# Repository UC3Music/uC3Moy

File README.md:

uC3Moy
======

UC3Music-e version of the CMoy pocket headphone amplifier (originally designed by Chu Moy )

Designed to fit in to a Smint* can.
Smint sweets can inner dimensions: 69mm x 36mm x 17mm. Outer dimensions: 77mm x 40mm x 21mm.

Designed to work on a single 6LR61 9V battery (alcaline or rechargeable). Draws about 8mA of current at regular listening levels (13mA at full output). Lithium technology coming soon.

It might get loud, use responsibly.

>*Smint is a mint sweet similar to Wrigley's Eclipse

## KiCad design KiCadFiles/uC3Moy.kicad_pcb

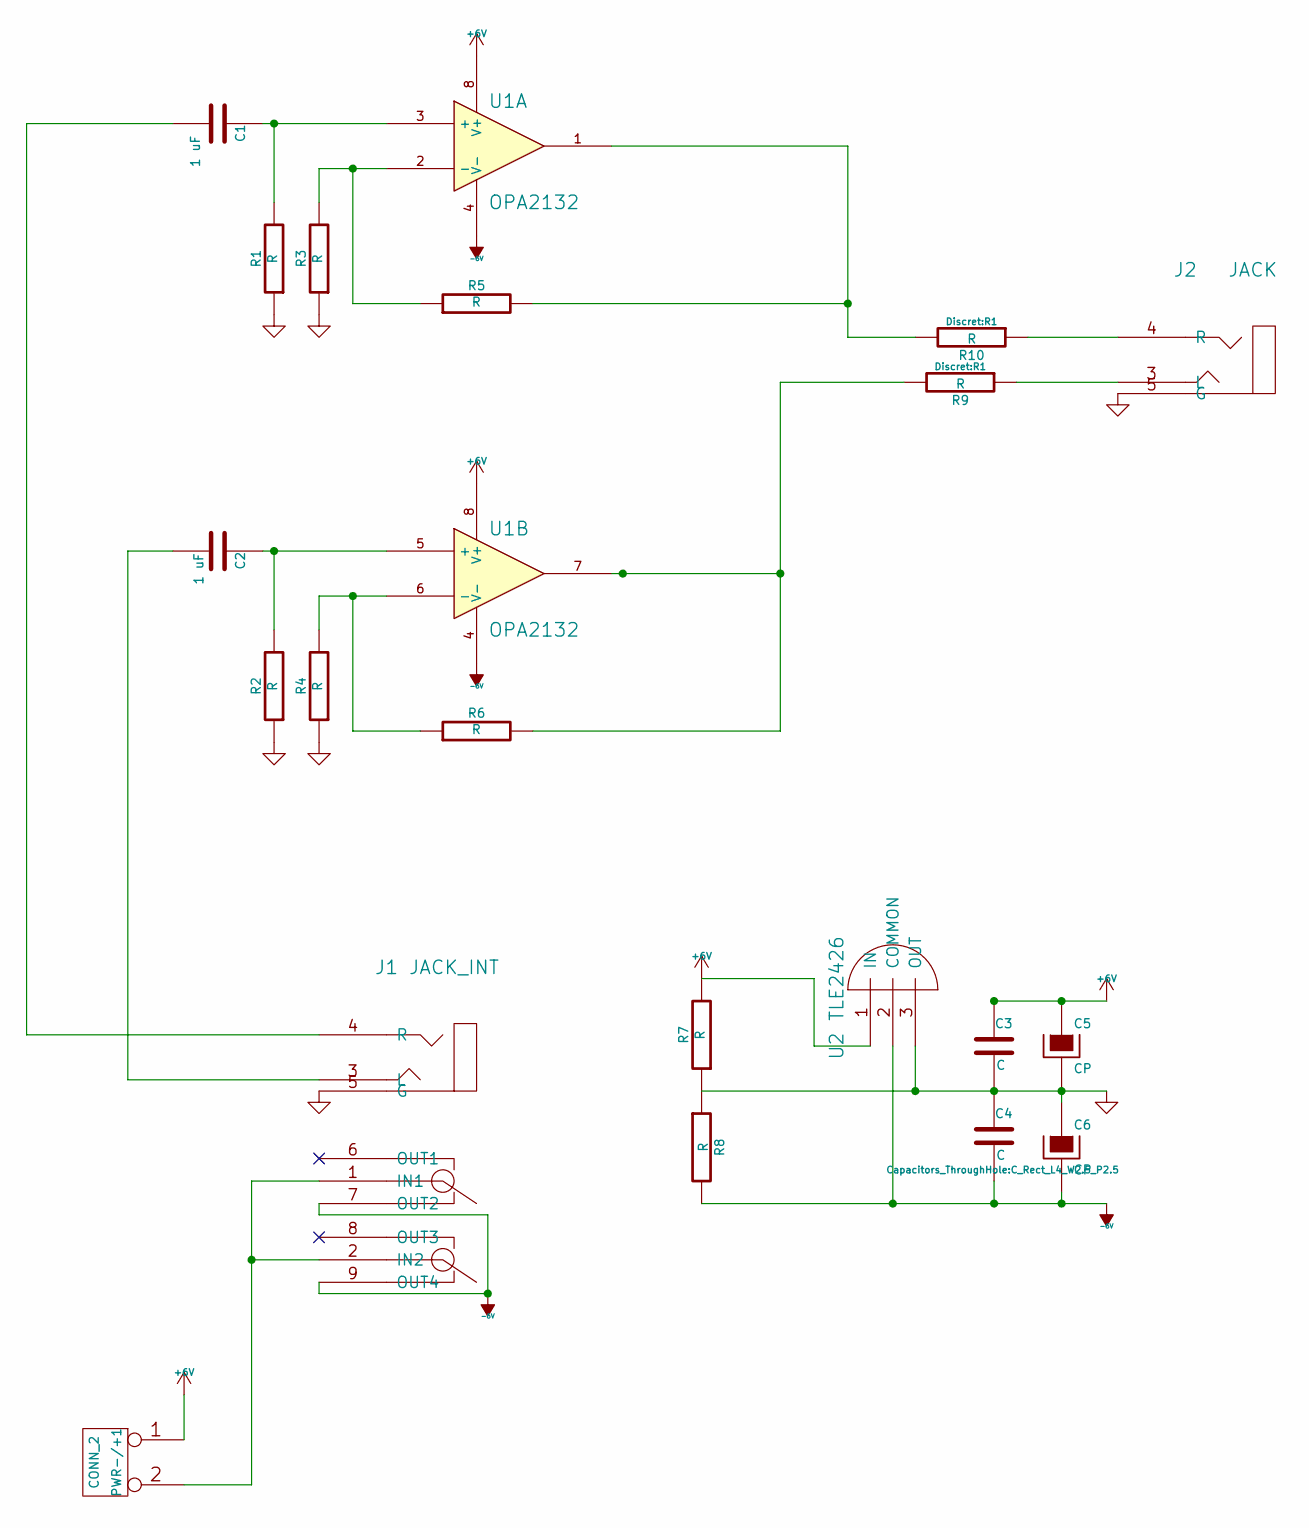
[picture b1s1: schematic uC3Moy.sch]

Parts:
C1, C2: 1 uF; C_Rect_L7_W2.5_P5
C3, C4: C; C_Rect_L4_W2.5_P2.5
C5, C6: CP; C_Radial_D5_L6_P2.5
J1: JACK_INT; jackint
J2: JACK; jack
PWR-/+1: CONN_2; Pin_Header_Straight_1x02
R1, R2, R3, R4, R5, R6, R7, R8, R9, R10: R; R1
U1: OPA2132; DIP-8_W7.62mm_jorfru
U2: TLE2426; TO-92_Inline_Wide

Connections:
+6V: C3.1, C5.1, PWR-/+1.1, R7.2, U1.8 (V+), U2.1 (IN)
-6V: C4.2, C6.2, J1.7 (OUT2), J1.9 (OUT4), R8.2, U1.4 (V-), U2.2 (COMMON)
GND: C3.2, C4.1, C5.2, C6.1, J1.5 (G), J2.5 (G), R1.1, R2.1, R3.1, R4.1, R7.1, R8.1, U2.3 (OUT)
unnamed: C1.1, R1.2, U1.3 (+)
unnamed: C1.2, J1.4 (R)
unnamed: C2.1, R2.2, U1.5 (+)
unnamed: C2.2, J1.3 (L)
unnamed: J1.1 (IN1), J1.2 (IN2), PWR-/+1.2 (PM)
unnamed: J2.3 (L), R9.1
unnamed: J2.4 (R), R10.1
unnamed: R3.2, R5.1, U1.2 (-)
unnamed: R4.2, R6.1, U1.6 (-)
unnamed: R6.2, R9.2, U1.7
unnamed: R5.2, R10.2, U1.1

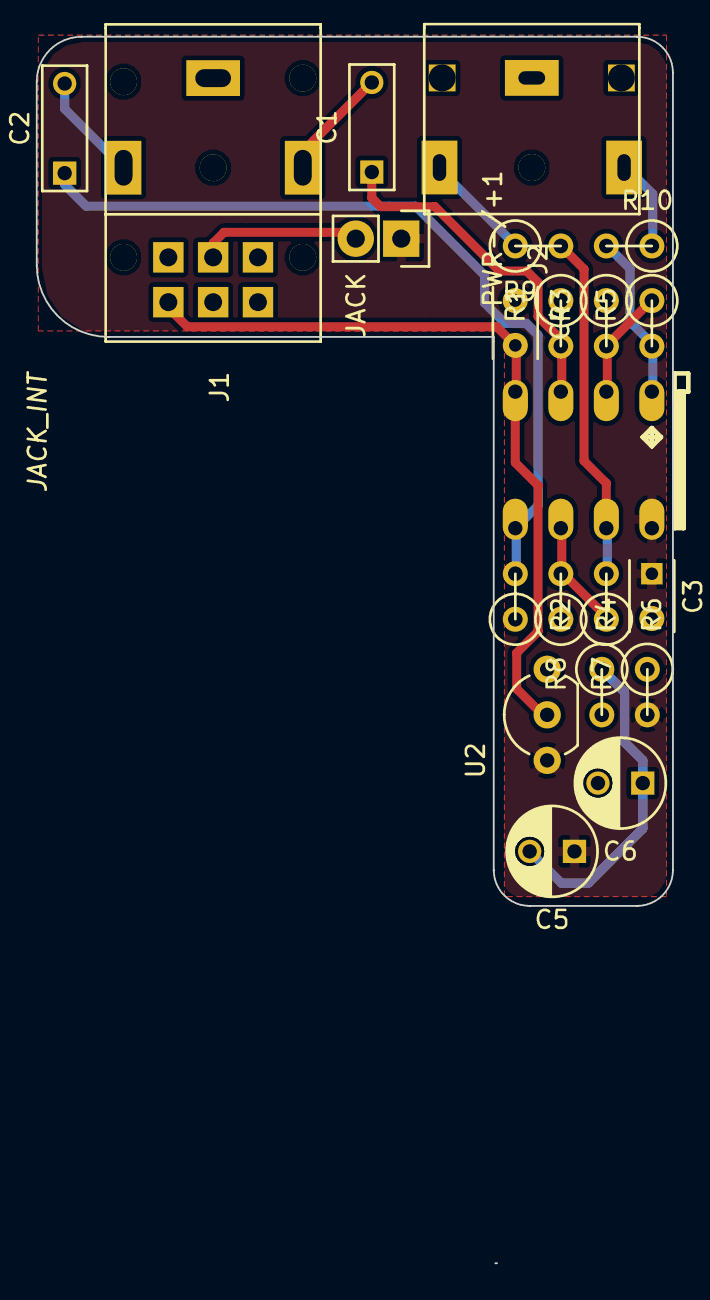
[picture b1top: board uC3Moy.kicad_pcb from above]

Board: 2 copper layers, 35.5 x 68.4 mm, 21 parts (0 on the bottom side), 14 nets.

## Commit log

2014-11-22 Added schematic (without connectors).
2014-11-22 Added gitignore for *.bak files
2015-03-02 Commit subiendo el diseño principal
2015-03-02 General UPLOAD
    PCB folder created.
    >Media folder containing .jpg images of PCB created.
    >KiCadFiles folder containing KiCad files of PCB created.
    >gerber folder containing gerber files of PCB created.
    A .pdf file containing a drawing of the schematic added.
2015-03-06 README revision
2015-03-06 Schematic on .pdf added to Media folder
2015-03-14 Modified lenght to fit under 50x50mm boards
2015-03-15 redo gerbers
2015-03-15 Silkscreen upgrades
2015-03-16 guitar logo added to back silkscreen
2015-03-17 Updates in bottom silkescreen
2015-03-17 updated gerbers
2015-03-17 With logo
2015-03-19 substracted soldermask from silkscreen
2015-03-19 v0.1 gerber files sended to SeeedStudio
2015-07-11 Added photos and media
2015-11-04 savepoint
2015-11-05 Ready to rock!
2015-11-05 uploaded gerber.zip
2015-11-05 Ready to rock
2015-11-13 Big and spaaaaacy oval pads. Ready to rock. Gerbers sent to PCBWay. V2.0 finished
2016-10-08 Updated README
    Me equivoqué en una letra, y qué?
    Pues que tiene que quedar decoroso, leñe!
